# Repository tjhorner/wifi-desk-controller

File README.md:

# WiFi Desk Controller

This repository includes the source files for my WiFi Desk Controller design.

- `firmware`: The stock ESPHome-based firmware that's available from the GitHub Releases and [my website](https://shop.horner.tj/things/desk-controller/setup/stock)
- `enclosure`: Fusion 360 source, STL, and STEP files for the 3D-printable enclosure
- `pcb`: KiCad project files for the PCB

You may also find the associated [ESPHome custom component](https://github.com/tjhorner/esphome-standing-desk) interesting if you want to implement your own desk brand, or just dive deeper into how the firmware works.

## Stock Firmware

The stock firmware is ESPHome-based, and contains a bunch of components that are useful for setup. It exposes these entities:

- Desk Height: reports desk height as reported by control box
- Target Desk Height: changes the target desk height
- Desk Preset 1: sets the desk height to preset 1
- Desk Preset 2: sets the desk height to preset 2
- Desk Preset 3: sets the desk height to preset 3
- Desk Preset 4: sets the desk height to preset 4

The stock firmware is automatically built for each supported desk on release. There is a [GitHub Actions workflow](.github/workflows/build.yaml) which handles this. The `make-stock-bin` script replaces the `DESK_BRAND` in the [stock config.yaml](firmware/config.yaml) with the appropriate config and builds it. It runs this script for each of the supported desk brands in the build matrix, then uploads a release artifact.

If you would like to contribute compatibility for a new desk, you first need to submit a pull request to [this repo](https://github.com/tjhorner/esphome-standing-desk/tree/master/configs/desks) which adds a config file for the desk (and, if necessary, a new protocol decoder for it). See [Desk Compatibility](https://github.com/tjhorner/wifi-desk-controller/wiki/Desk-Compatibility) for more info on adding a new desk brand.

## License

The ESPHome configs are licensed under MIT; everything else (enclosure and PCB design) are CC BY-NC-SA 4.0. The appropriate license files are available in the root of the repo.

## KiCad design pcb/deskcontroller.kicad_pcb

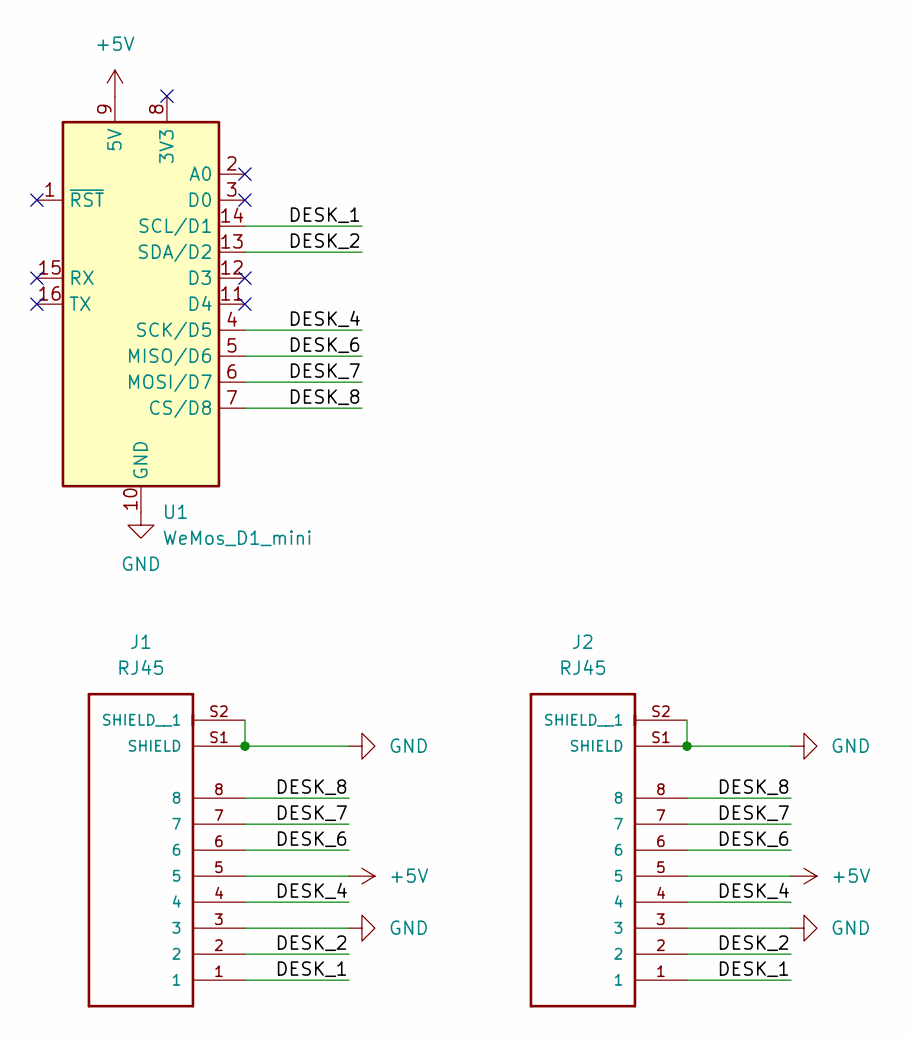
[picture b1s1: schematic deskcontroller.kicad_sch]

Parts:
J1, J2: RJ45; ASSMANN_A-2004-2-4-LPS-N-R; PARTREV 00
U1: WeMos_D1_mini; WEMOS_D1_mini_light

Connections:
+5V: J1.5, J2.5, U1.9 (5V)
/DESK_1: J1.1, J2.1, U1.14 (SCL/D1)
/DESK_2: J1.2, J2.2, U1.13 (SDA/D2)
/DESK_4: J1.4, J2.4, U1.4 (SCK/D5)
/DESK_6: J1.6, J2.6, U1.5 (MISO/D6)
/DESK_7: J1.7, J2.7, U1.6 (MOSI/D7)
/DESK_8: J1.8, J2.8, U1.7 (CS/D8)
GND: J1.3, J1.S1 (SHIELD), J1.S2 (SHIELD__1), J2.3, J2.S1 (SHIELD), J2.S2 (SHIELD__1), U1.10 (GND)

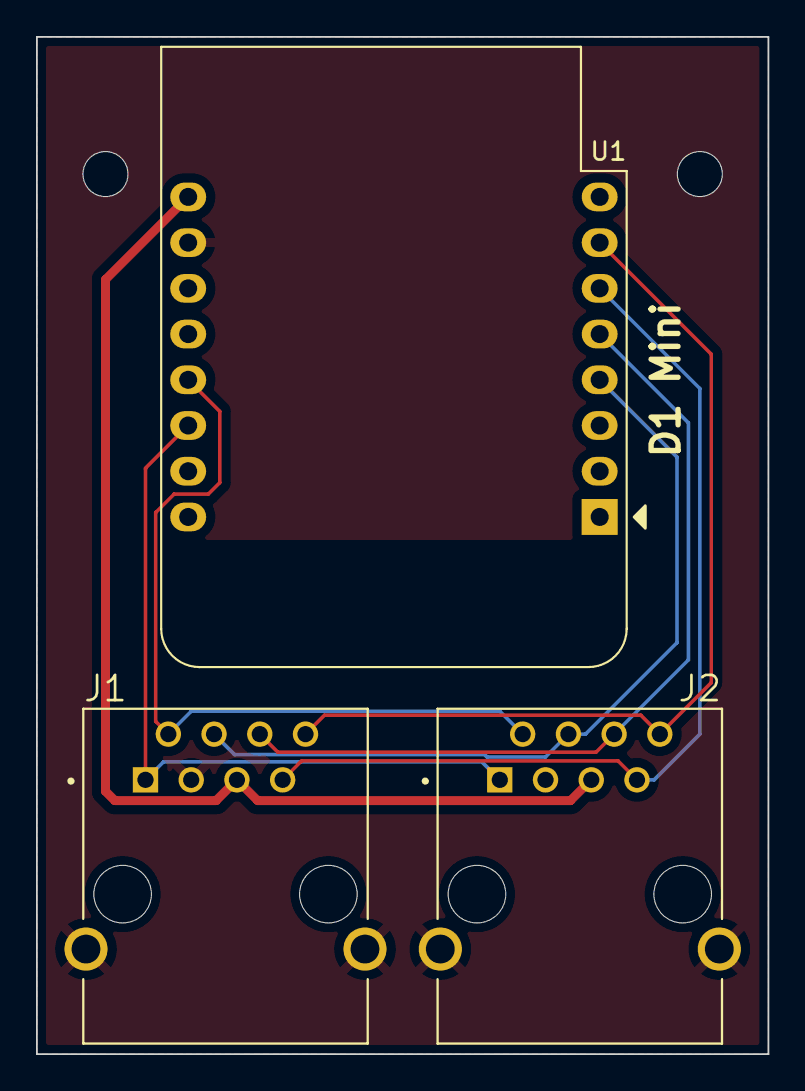
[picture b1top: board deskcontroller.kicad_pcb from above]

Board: 2 copper layers, 40.6 x 56.5 mm, 3 parts (0 on the bottom side), 8 nets.

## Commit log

2022-05-16 firmware
2022-05-16 macos cringe
2022-05-16 enable logging and improv
2022-05-16 add home assistant API to stock firmware
2022-05-16 Fully Jarvis config
2022-05-22 PCB and enclosure source, docs
2022-05-22 jesus christ, DS_Store
2022-05-30 add http api and disable reboot timeout
2022-05-31 0.0.7 config
2022-05-31 licenses
2022-06-01 Fix project namespace
2022-06-01 Reference other project in readme
2022-06-08 add issue template
2022-06-08 lol oops
2022-06-08 firmware docs
2022-06-11 add test firmware
2022-06-15 fix silly issue
2022-06-17 Experimental version of firmware for hidden network capability
2022-06-19 fix readme link
2022-06-20 Experimental presets support
2022-06-20 remove that weird ssid
2022-06-20 readme
